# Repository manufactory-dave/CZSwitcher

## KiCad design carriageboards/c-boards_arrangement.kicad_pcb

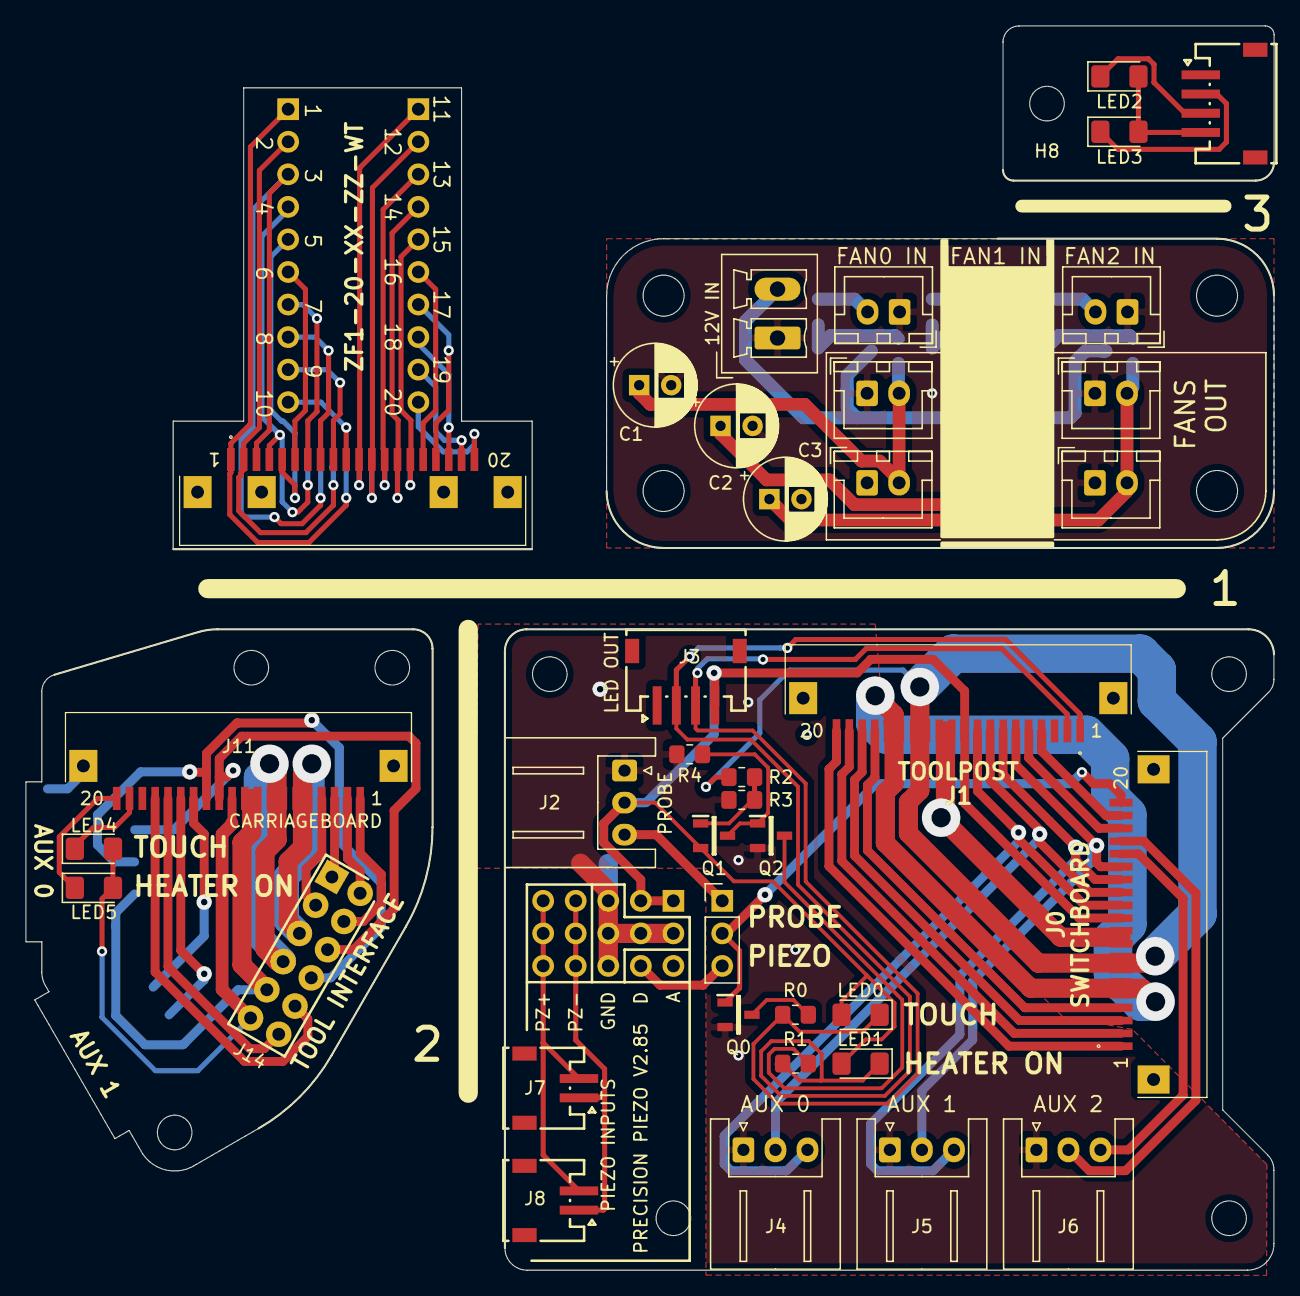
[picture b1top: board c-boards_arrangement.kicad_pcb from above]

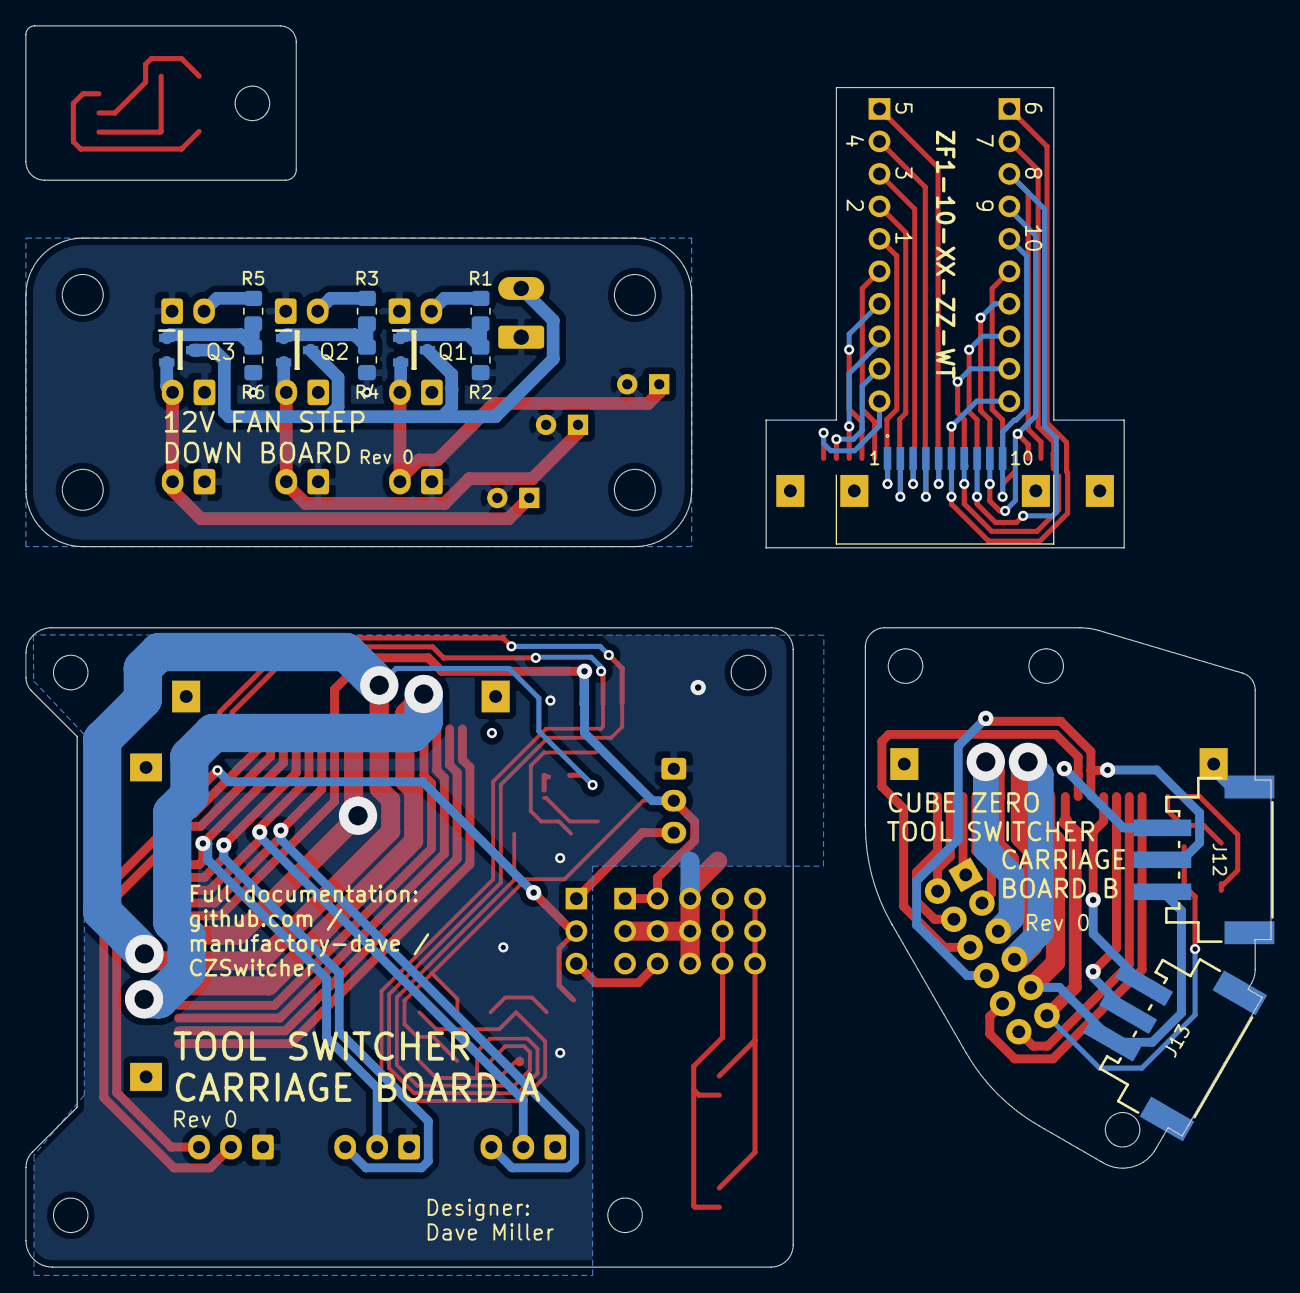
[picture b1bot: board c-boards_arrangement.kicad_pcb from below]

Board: 2 copper layers, 97.4 x 97.1 mm, 68 parts (12 on the bottom side), 75 nets.

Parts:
C1, C2, C3: 100uF_35V_Electro_Radial; CP_Radial_D6.3mm_P2.50mm
H1, H2, H3, H4, H5, H6, H7, H8: MountingHole; MountingHole_2.7mm_M2.5
H1#2, H2#2, H3#2, H4#2: MountingHole; MountingHole_3.2mm_M3
J0: SWITCHBOARD; ZF1-20-XX-ZZ-WT_Handsolder
J1: TOOLPOST; ZF1-20-XX-ZZ-WT_Handsolder
J1#2: 12V IN; PhoenixContact_MCV_1,5_2-G-3.81_1x02_P3.81mm_Vertical
J2: PROBE; JST_XH_S3B-XH-A_1x03_P2.50mm_Horizontal
J2#2: FAN0 IN; JST_XH_B2B-XH-A_1x02_P2.50mm_Vertical
J3, J10: STATUS LED; JST-ZH_S4B-ZR-SM4A-TF
J3#2, J4#2: FAN0 OUT; JST_XH_B2B-XH-A_1x02_P2.50mm_Vertical
J4: AUX 0; JST_XH_S3B-XH-A_1x03_P2.50mm_Horizontal
J5: AUX 1; JST_XH_S3B-XH-A_1x03_P2.50mm_Horizontal
J5#2: FAN1 IN; JST_XH_B2B-XH-A_1x02_P2.50mm_Vertical
J6: AUX 2; JST_XH_S3B-XH-A_1x03_P2.50mm_Horizontal
J6#2, J7#2: FAN1 OUT; JST_XH_B2B-XH-A_1x02_P2.50mm_Vertical
J7: PIEZO 1; JST-ZH_S2B-ZR-SM4A-TF
J8: PIEZO 2; JST-ZH_S2B-ZR-SM4A-TF
J8#2: FAN2 IN; JST_XH_B2B-XH-A_1x02_P2.50mm_Vertical
J9, J10#2: FAN2 OUT; JST_XH_B2B-XH-A_1x02_P2.50mm_Vertical
J11: CARRIAGEBOARD; ZF1-20-XX-ZZ-WT_Handsolder
J12: AUX 0; JST-XH_2.50MM_03x01_SMT
J13: AUX 1; JST-XH_2.50MM_03x01_SMT
J14: TOOL INTERFACE; 813-S1-012-10-014101
JP0: PIEZO / PROBE SELECT; PinHeader_1x03_P2.54mm_Vertical
LED0, LED2, LED4: APTD3216LVBC_D; LED_1206_3216Metric_Pad1.42x1.75mm_HandSolder
LED1, LED3, LED5: APTD3216LSYCK; LED_1206_3216Metric_Pad1.42x1.75mm_HandSolder
PCB0: PrecisionPiezo285; Precision_Piezo_2.85
Q0, Q2: DMN3150L-7; SUPER-SOT-3
Q1: NTR1P02T1G; SUPER-SOT-3
Q1#2, Q2#2, Q3: FDN359BN; SUPER-SOT-3
R0: 39R; R_0805_2012Metric_Pad1.20x1.40mm_HandSolder
R1: 51R; R_0805_2012Metric_Pad1.20x1.40mm_HandSolder
R1#2, R2, R3, R3#2, R5: 39k; R_0805_2012Metric_Pad1.20x1.40mm_HandSolder
R2#2, R4#2, R6: 10k; R_0805_2012Metric_Pad1.20x1.40mm_HandSolder
R4: 220R; R_0805_2012Metric_Pad1.20x1.40mm_HandSolder
ax13, ax17: Conn_01x10; PinHeader_1x10_P2.54mm_Vertical
ax15: ZF1-20-XX-ZZ-WT; ZF1-20-XX-ZZ-WT_Handsolder
ax16: ZF1-10-XX-ZZ-WT; ZF1-10-XX-ZZ-WT_Handsolder

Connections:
+3V3: J0.11, J1.10, J2.2, J3.4, LED0.2, LED1.2, PCB0.1, PCB0.2, Q1.2
+12V: J1#2.2, Q1#2.3, Q2#2.3, Q3.3
+24V: J0.5, J0.6, J1.15, J1.16
/1A: J0.4, J1.17
/1A_1: J11.4, J14.3
/1B: J0.1, J1.20
/1B_1: J11.1, J14.4
/2A: J0.3, J1.18
/2A_1: J11.3, J14.1
/2B: J0.2, J1.19
/2B_1: J11.2, J14.2
/3V3_1: J11.11, J14.11, LED4.2, LED5.2
/24V_1: J11.5, J11.6, J14.5
/AUX0: J0.13, J1.8, J4.2
/AUX0_1: J11.13, J12.2, J14.8
/AUX1: J0.15, J1.6, J5.2
/AUX1_1: J11.15, J13.2
/AUX2: J0.17, J6.2
/FAN0_OUT: C1.1, J3#2.2, J4#2.2, Q1#2.2
/FAN1_OUT: C2.1, J6#2.2, J7#2.2, Q2#2.2
/FAN2_OUT: C3.1, J9.2, J10#2.2, Q3.2
/GND1_1: J11.16, J14.12
/GND_1: J11.9, J11.10, J12.1, J13.1, J14.9
/HEATER_OUT: J0.7, J0.8, J1.13, J1.14, R2.1
/HEATER_OUT_1: J11.7, J11.8, J14.7
/HEATLED-: J1.1, J3.2, LED1.1, R1.1
/HEATLED-_1: J11.20, LED5.1
/PROBE: J0.20, JP0.2, Q0.1
/PROBELED-: J1.2, J3.3, LED0.1, R0.1
/PROBELED-_1: J11.19, LED4.1
/PZ+: J7.2, J8.2, PCB0.5, PCB0.10, PCB0.15
/PZ-: J7.1, J8.1, PCB0.4, PCB0.9, PCB0.14
/THERM_OUT: J0.19, J1.4
/THERM_OUT_1: J11.17, J14.10
/V_AUX0: J0.12, J1.9, J4.3
/V_AUX0_1: J11.12, J12.3, J14.6
/V_AUX1: J0.14, J1.7, J5.3
/V_AUX1_1: J11.14, J13.3
/V_AUX2: J0.16, J6.3
GND: C1.2, C2.2, C3.2, J0.9, J0.10, J1.11, J1.12, J1#2.1, J2.1, J2#2.1, J3#2.1, J4.1, J4#2.1, J5.1, J5#2.1, J6.1, J6#2.1, J7#2.1, J8#2.1, J9.1, J10#2.1, PCB0.3, PCB0.6, PCB0.7, PCB0.8, PCB0.13, Q0.2, Q2.2, R2#2.2, R3.2, R4.2, R4#2.2, R6.2
GND1: J0.18, J1.5
unnamed: J2#2.2, R1#2.1
unnamed: J2.3, JP0.1
unnamed: J5#2.2, R3#2.1
unnamed: J8#2.2, R5.1
unnamed: J10.2, LED3.1
unnamed: J10.3, LED2.1
unnamed: J10.4, LED2.2, LED3.2
unnamed: JP0.3, PCB0.12
unnamed: Q0.3, R0.2
unnamed: Q1.1, Q1#2.1, R1#2.2, R2.2, R2#2.1, R3.1
unnamed: Q1.3, Q2.1, R4.1
unnamed: Q2#2.1, R3#2.2, R4#2.1
unnamed: Q2.3, R1.2
unnamed: Q3.1, R5.2, R6.1
unnamed: ax13.1, ax15.11, ax16.5
unnamed: ax13.2, ax15.12, ax16.4
unnamed: ax13.3, ax15.13, ax16.3
unnamed: ax13.4, ax15.14, ax16.2
unnamed: ax13.5, ax15.15, ax16.1
unnamed: ax13.6, ax15.16
unnamed: ax13.7, ax15.17
unnamed: ax13.8, ax15.18
unnamed: ax13.9, ax15.19
unnamed: ax13.10, ax15.20
unnamed: ax15.1, ax16.6, ax17.1
unnamed: ax15.2, ax16.7, ax17.2
unnamed: ax15.3, ax16.8, ax17.3
unnamed: ax15.4, ax16.9, ax17.4
unnamed: ax15.5, ax16.10, ax17.5
unnamed: ax15.6, ax17.6
unnamed: ax15.7, ax17.7
unnamed: ax15.8, ax17.8
unnamed: ax15.9, ax17.9
unnamed: ax15.10, ax17.10

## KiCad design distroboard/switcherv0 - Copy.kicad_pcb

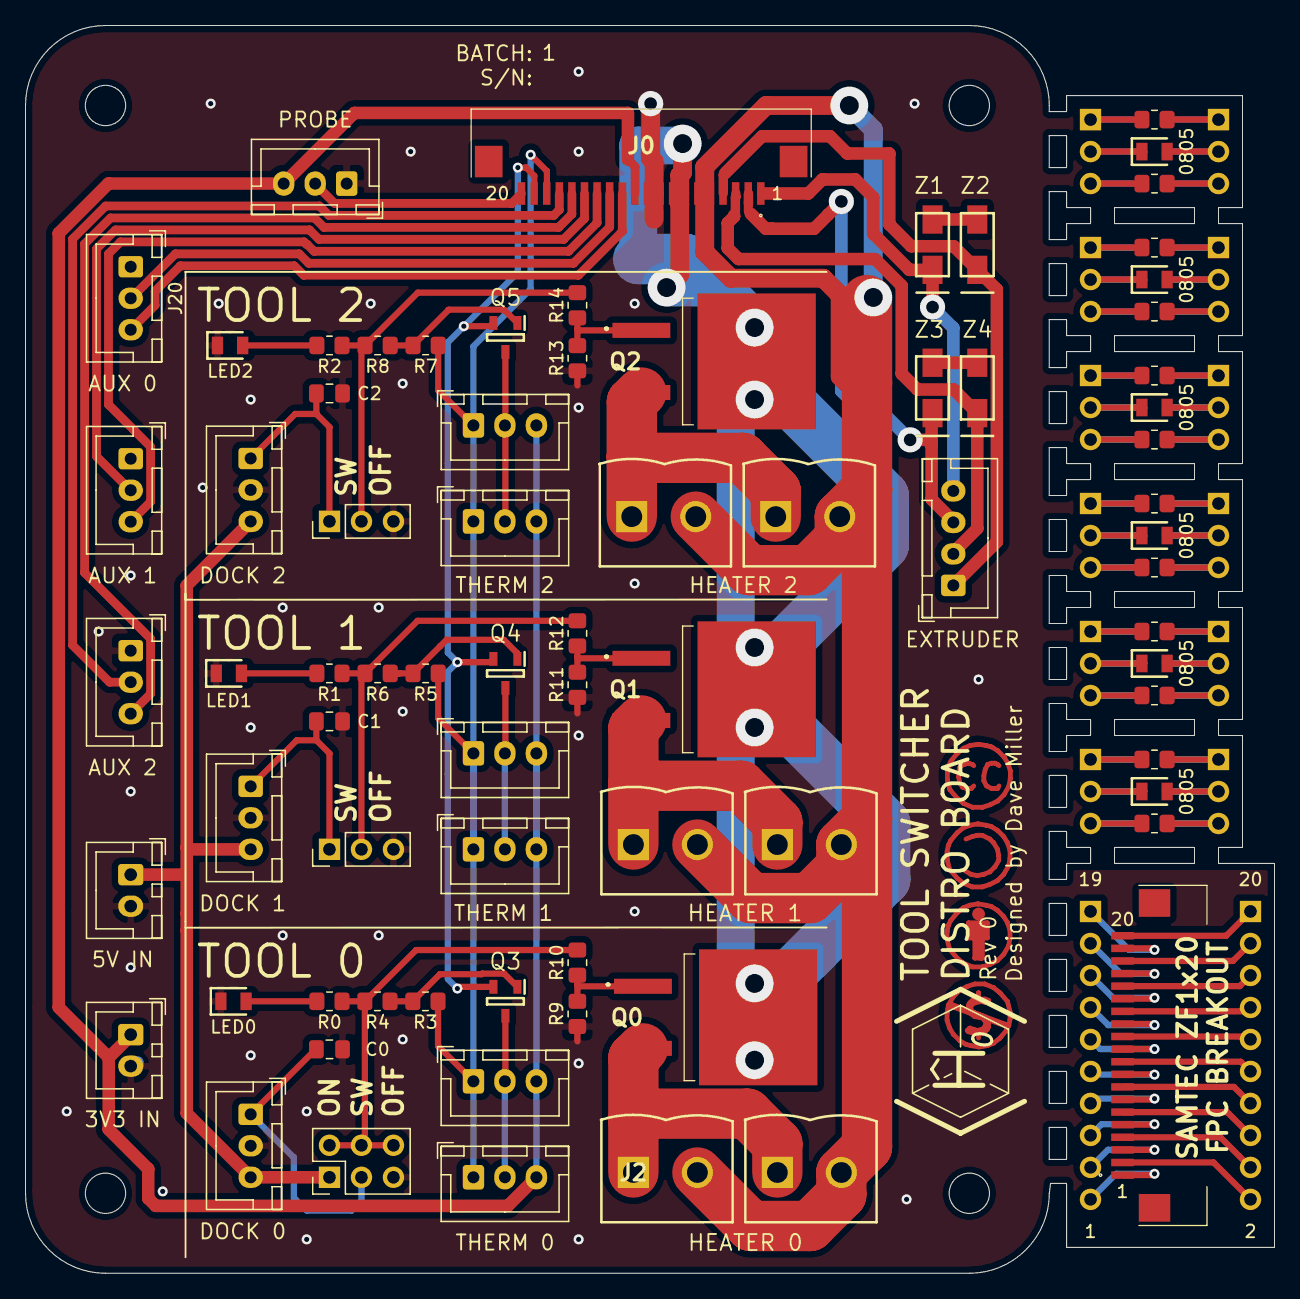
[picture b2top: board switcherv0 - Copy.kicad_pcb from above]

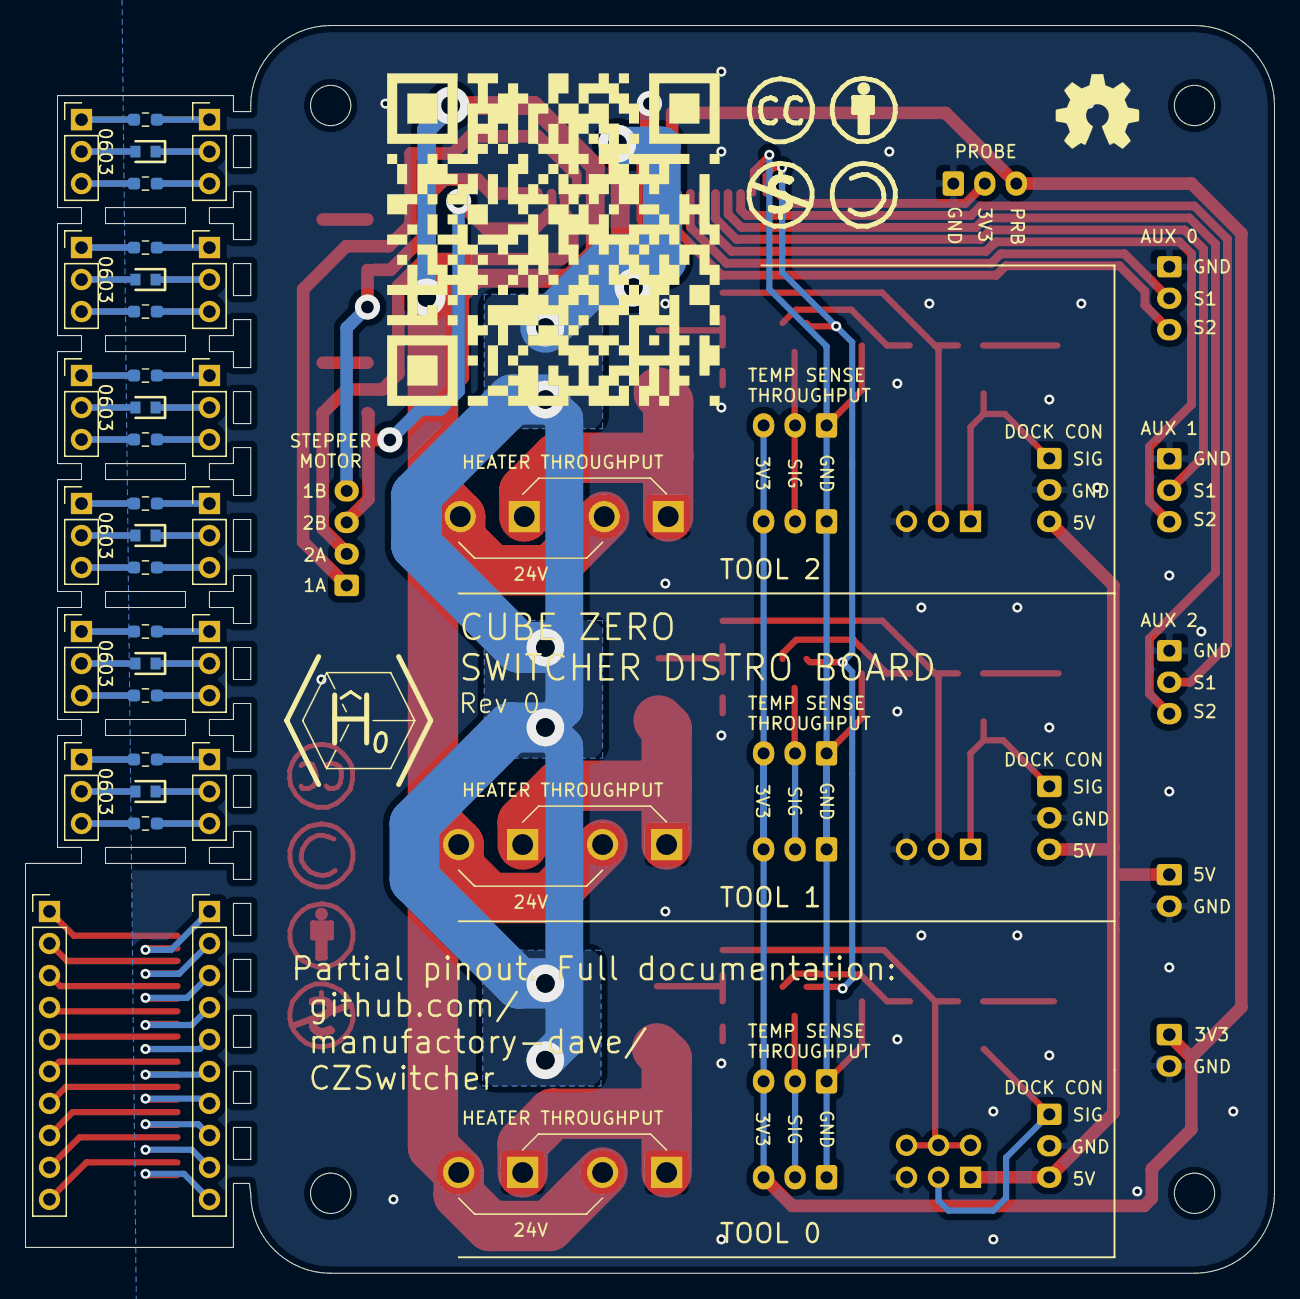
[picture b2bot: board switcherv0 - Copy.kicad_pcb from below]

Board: 2 copper layers, 99.2 x 99.1 mm, 76 parts (8 on the bottom side), 41 nets.

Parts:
C0, C1, C2: 100nF; C_0805_2012Metric_Pad1.18x1.45mm_HandSolder
H0, H1, H2, H3: MountingHole; MountingHole_3.2mm_M3_DIN965
J0: CARRIAGE CONNECTOR; ZF1-20-XX-ZZ-WT
J1: MOTOR IN; JST_XH_B4B-XH-A_1x04_P2.50mm_Vertical
J2, J3: HEATER 0; SHDR2W102P0X508_1X2_1016X835X1230P
J4, J5: HEATER 1; SHDR2W102P0X508_1X2_1016X835X1230P
J6, J7: HEATER 2; SHDR2W102P0X508_1X2_1016X835X1230P
J8, J9: THERM 0; JST_XH_B3B-XH-A_1x03_P2.50mm_Vertical
J10, J11: THERM 1; JST_XH_B3B-XH-A_1x03_P2.50mm_Vertical
J12, J13: THERM 2; JST_XH_B3B-XH-A_1x03_P2.50mm_Vertical
J14: DOCK 0; JST_XH_B3B-XH-A_1x03_P2.50mm_Vertical
J15: DOCK 1; JST_XH_B3B-XH-A_1x03_P2.50mm_Vertical
J16: DOCK 2; JST_XH_B3B-XH-A_1x03_P2.50mm_Vertical
J17: 5V IN; JST_XH_B2B-XH-A_1x02_P2.50mm_Vertical
J18: 3V3 IN; JST_XH_B2B-XH-A_1x02_P2.50mm_Vertical
J19: PROBE; JST_XH_B3B-XH-A_1x03_P2.50mm_Vertical
J20: AUX 0; JST_XH_B3B-XH-A_1x03_P2.50mm_Vertical
J21: AUX 1; JST_XH_B3B-XH-A_1x03_P2.50mm_Vertical
J22: AUX 2; JST_XH_B3B-XH-A_1x03_P2.50mm_Vertical
J**: ZF1-20-XX-ZZ-WT
JP0: TOOL 0 JUMPER; PinHeader_2x03_P2.54mm_Vertical
JP1: TOOL 1 JUMPER; PinHeader_1x03_P2.54mm_Vertical
JP2: TOOL 2 JUMPER; PinHeader_1x03_P2.54mm_Vertical
LED0, LED1, LED2: KP-2012SYC; LEDC2012X110N
LED**: LEDC2012X110N
LED**#2, LED**#4, LED**#5, LED**#7, LED**#9, LED**#11: LEDC1608X120N
LED**#3, LED**#6, LED**#8, LED**#10, LED**#12: LEDC2012X110N
Q0, Q1, Q2: IPB034N03LGATMA1
Q3, Q4, Q5: FDN359BN; SOT95P251X112-3N
QR1: GithubQR; githubQR08
R0, R1, R2: 125; R_0805_2012Metric_Pad1.20x1.40mm_HandSolder
R3, R5, R7: 10k; R_0805_2012Metric_Pad1.20x1.40mm_HandSolder
R4, R6, R8, R10, R12, R14: 22; R_0805_2012Metric_Pad1.20x1.40mm_HandSolder
R9, R11, R13: 10K; R_0805_2012Metric_Pad1.20x1.40mm_HandSolder
U1: CubeZeroLogo; CubeZeroLogoFP
Z1, Z2, Z3, Z4: PTZTE2527A; DIOM5026X220N

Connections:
+3V3: J0.11, J8.3, J9.3, J10.3, J11.3, J12.3, J13.3, J18.1, J19.3
+5V: J14.3, J15.3, J16.3, J17.1, JP0.1
+24V: J0.5, J0.6, J2.2, J3.2, J4.2, J5.2, J6.2, J7.2
/1A: J0.4, J1.1, Z2.1
/1B: J0.1, J1.4, Z1.1
/2A: J0.3, J1.2, Z4.1
/2B: J0.2, J1.3, Z3.1
/AUX0: J0.13, J20.2
/AUX1: J0.15, J21.2
/AUX2: J0.17, J22.2
/HEATER_OUT: J0.7, J0.8, Q0.2, Q1.2, Q2.2
/PROBE: J0.20, J19.2
/THERM_0: J8.2, J9.2, Q3.3
/THERM_1: J10.2, J11.2, Q4.3
/THERM_2: J12.2, J13.2, Q5.3
/THERM_OUT: J0.19, Q3.2, Q4.2, Q5.2
/TOOL0_LOGIC: JP0.2, JP0.4, JP0.6, R0.1, R4.2, R10.2
/TOOL1_LOGIC: JP1.2, R1.1, R6.2, R12.2
/TOOL2_LOGIC: JP2.2, R2.1, R8.2, R14.2
/Tool0Sig: C0.1, J14.1, JP0.3
/Tool1Sig: C1.1, J15.1, JP1.1
/Tool2Sig: C2.1, J16.1, JP2.1
/V_AUX0: J0.12, J20.3
/V_AUX1: J0.14, J21.3
/V_AUX2: J0.16, J22.3
GND: C0.2, C1.2, C2.2, J0.9, J0.10, J14.2, J15.2, J16.2, J17.2, J18.2, J19.1, J20.1, J21.1, J22.1, JP0.5, JP1.3, JP2.3, LED0.1, LED1.1, LED2.1, R9.1, R11.1, R13.1
GND1: J0.18, J8.1, J9.1, J10.1, J11.1, J12.1, J13.1, R3.1, R5.1, R7.1
unnamed: J2.1, J3.1, Q0.3
unnamed: J4.1, J5.1, Q1.3
unnamed: J6.1, J7.1, Q2.3
unnamed: LED0.2, R0.2
unnamed: LED1.2, R1.2
unnamed: LED2.2, R2.2
unnamed: Q0.1, R9.2, R10.1
unnamed: Q1.1, R11.2, R12.1
unnamed: Q2.1, R13.2, R14.1
unnamed: Q3.1, R3.2, R4.1
unnamed: Q4.1, R5.2, R6.1
unnamed: Q5.1, R7.2, R8.1
unnamed: Z1.2, Z2.2
unnamed: Z3.2, Z4.2

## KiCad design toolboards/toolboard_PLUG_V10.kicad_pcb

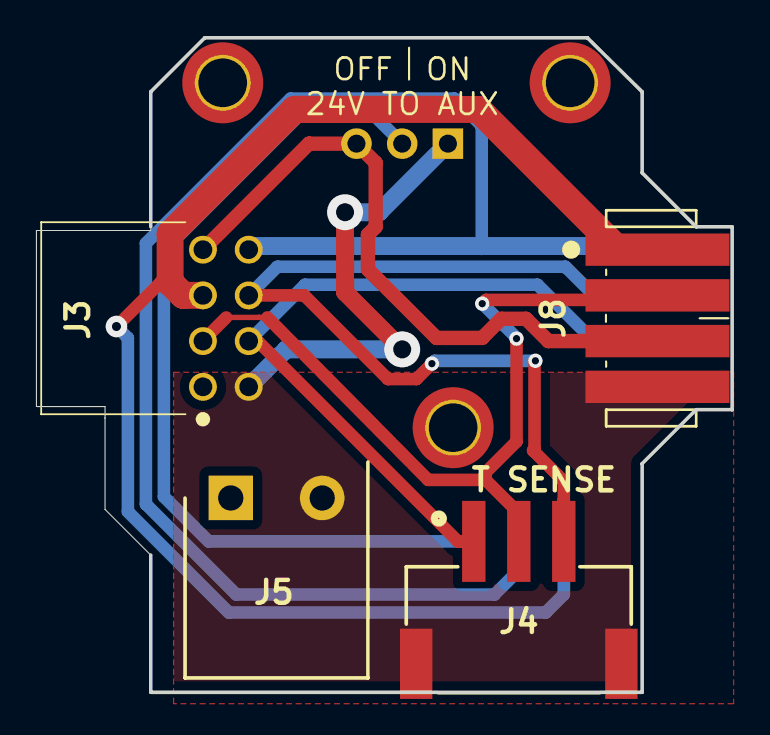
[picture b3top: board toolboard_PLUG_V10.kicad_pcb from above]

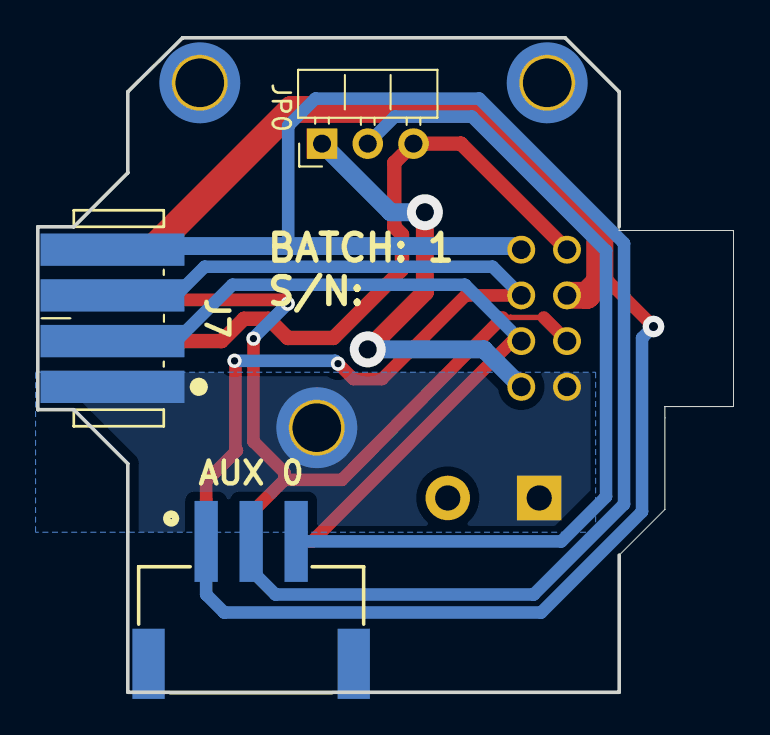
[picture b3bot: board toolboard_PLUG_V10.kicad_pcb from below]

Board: 2 copper layers, 38.6 x 36.4 mm, 10 parts (3 on the bottom side), 9 nets.

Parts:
H3, H4, H5: MountingHole_Pad; MountingHole_2.7mm_M2.5_ISO7380_Pad_TopBottom
J3: INTERBOARD B; SSW-104-XX-YYY-D-RA
J4: T SENSE; JST-XH_2.50MM_03x01_SMT
J5: HEATER; SHDRRA2W102P0X508_1X2_1016X1200X850P
J6: AUX 0; JST-XH_2.50MM_03x01_SMT
J7: DOCK INT 1; 8MM11000402131_handsolder
J8: DOCK INT 2; 8MM11000402131_handsolder
JP0: AUXO 24V SEL; PinHeader_1x03_P2.54mm_Horizontal

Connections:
/3V3_1: J3.6, J4.3, J7.3
/24V_1: J3.2, J4.4, J4.5, J5.2, J8.4, JP0.1
/AUX0_1: J3.8, J6.2, J7.4
/GND1_1: J3.4, J4.1, J7.2
/GND_1: J3.5, J6.1, J8.1
/HEATER_OUT_1: H4.1, J3.1, J5.1, J7.1
/THERM_OUT_1: J3.3, J4.2, J8.2
/V_AUX0_1: J3.7, J8.3, JP0.3
unnamed: J6.3, JP0.2

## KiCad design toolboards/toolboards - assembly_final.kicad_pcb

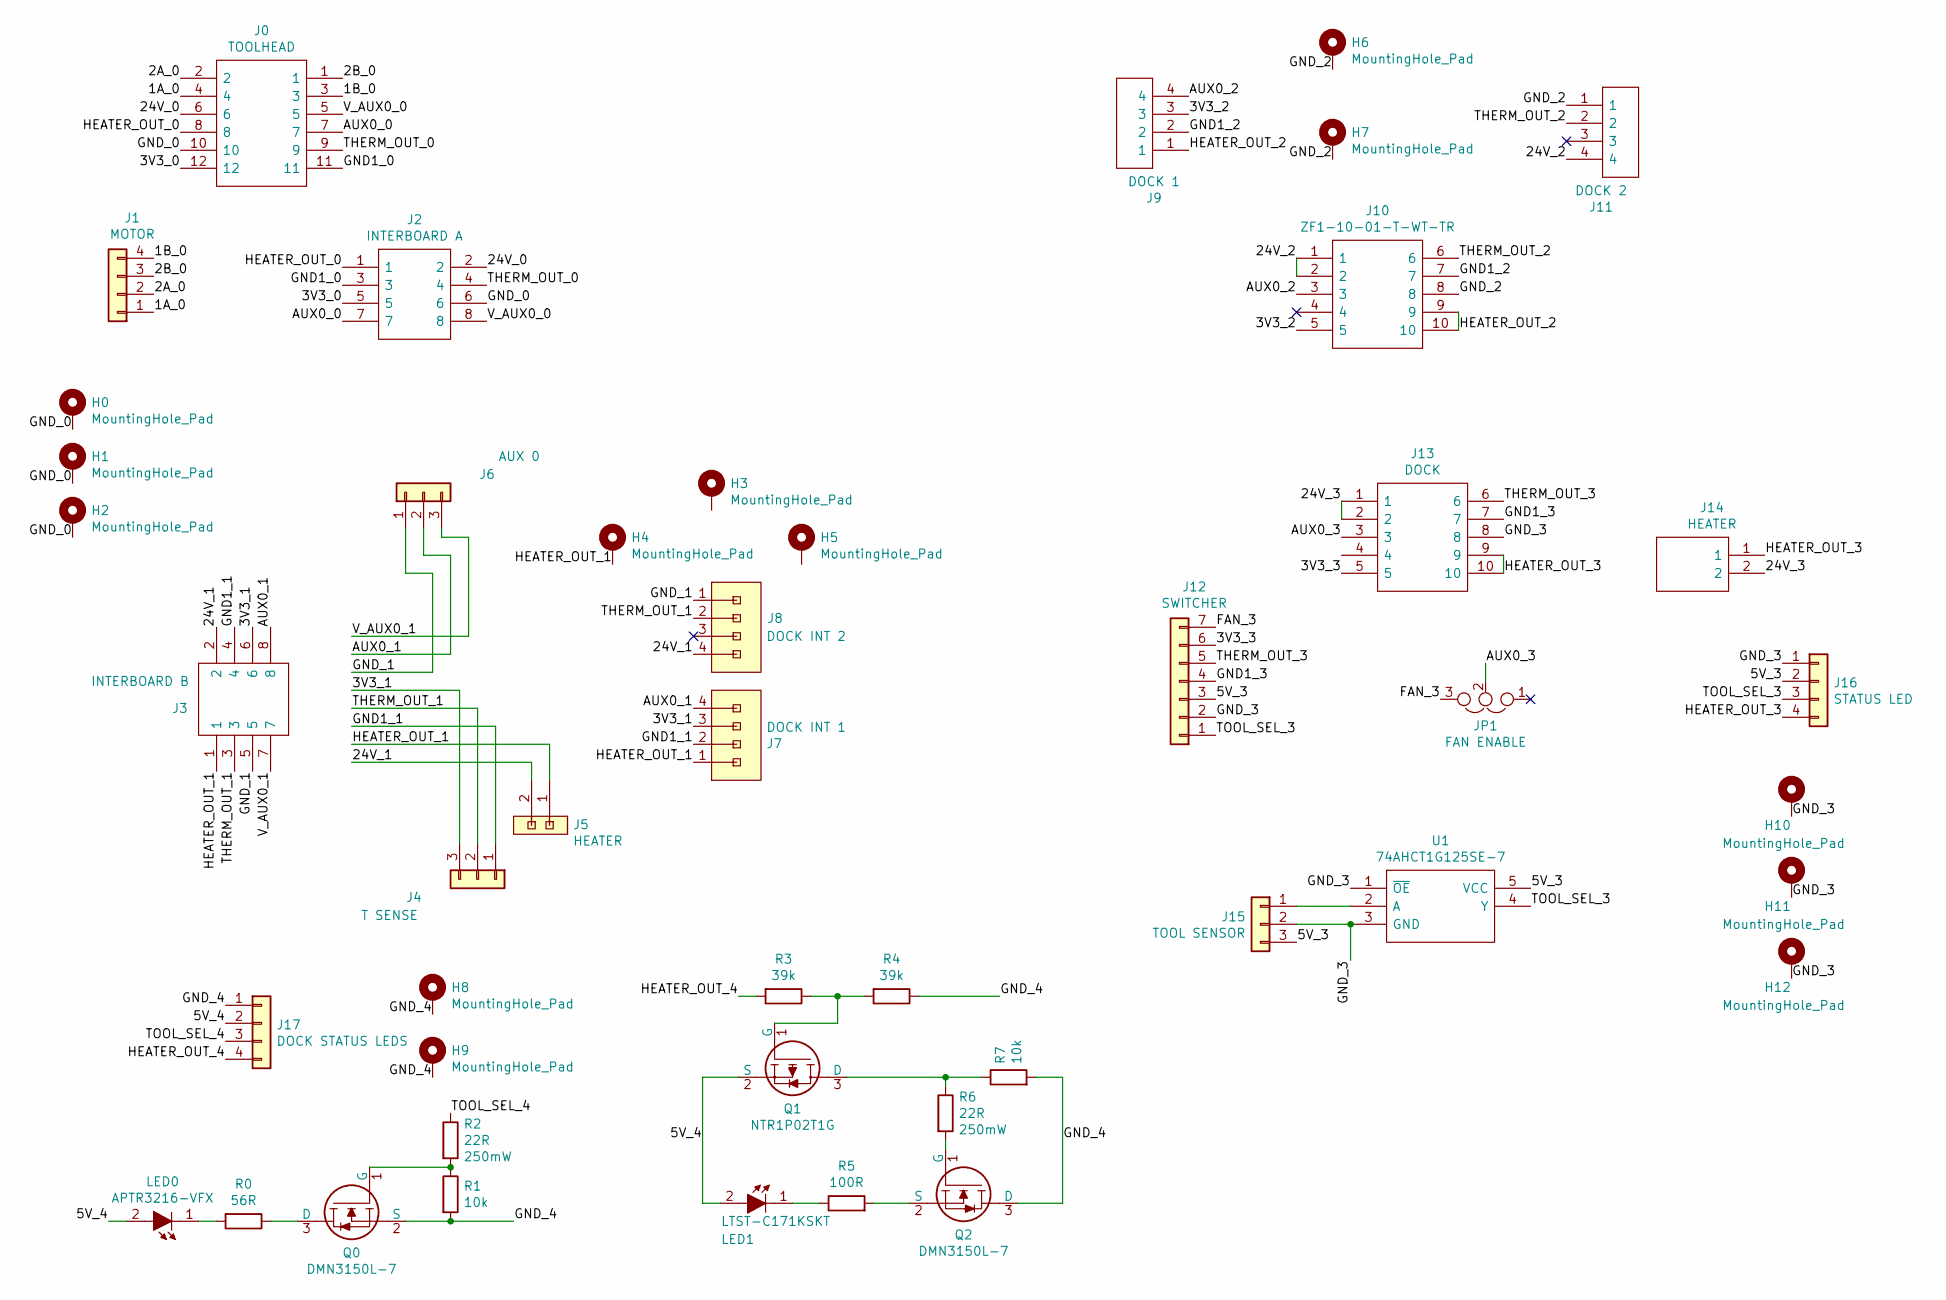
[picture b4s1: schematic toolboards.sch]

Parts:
H0, H1, H2, H3, H4, H5: MountingHole_Pad; MountingHole_2.7mm_M2.5_DIN965_Pad_TopBottom
H6, H7, H8, H9, H10, H11, H12: MountingHole_Pad; MountingHole_3.2mm_M3_DIN965_Pad_TopBottom
J0: TOOLHEAD; 8021001230507101_HS; Manufacturer_Part_Number 802-10-012-30-507101
J1: MOTOR; JST_XH_B4B-XH-A_1x04_P2.50mm_Vertical
J2: INTERBOARD A; HDRV8W64P254_2X4_1016X495X838P; Manufacturer_Part_Number TSW-104-07-T-D
J3: INTERBOARD B; SSW-104-XX-YYY-D-RA; Manufacturer_Part_Number SSW-104-02-T-D-RA
J4: T SENSE; JST-XH_2.50MM_03x01_SMT; Manufacturer_Part_Number S3B-XH-SM4-TB(LF)(SN)
J5, J14: HEATER; SHDRRA2W102P0X508_1X2_1016X1200X850P; Manufacturer_Part_Number 282815-2
J6: AUX 0; JST-XH_2.50MM_03x01_SMT; Manufacturer_Part_Number S3B-XH-SM4-TB(LF)(SN)
J7: DOCK INT 1; 8MM11000402131_handsolder
J8: DOCK INT 2; 8MM11000402131_handsolder
J9: DOCK 1; 811-S1-004-10-017101; Mouser Part Number 437-8MM11000402131
J10: ZF1-10-01-T-WT-TR; ZF1-10-XX-ZZ-WT_Handsolder; Manufacturer_Part_Number ZF1-10-01-T-WT-TR
J11: DOCK 2; 811-S1-004-10-017101; Mouser Part Number 437-8MM11000402131
J12: SWITCHER; JST_XH_B7B-XH-A_1x07_P2.50mm_Vertical
J13: DOCK; ZF1-10-XX-ZZ-WT_Handsolder; Manufacturer_Part_Number ZF1-10-01-T-WT-TR
J15: TOOL SENSOR; JST_XH_B3B-XH-A_1x03_P2.50mm_Vertical
J16: STATUS LED; JST-ZH_S4B-ZR-SM4A-TF; Part Number S4B-ZR-SM4A-TF
J17: DOCK STATUS LEDS; JST-ZH_S4B-ZR-SM4A-TF; Part Number S4B-ZR-SM4A-TF
JP1: FAN ENABLE; PinHeader_1x03_P2.54mm_Vertical
LED0: APTR3216-VFX; LED_1206_3216Metric_Pad1.42x1.75mm_HandSolder; Manufacturer_Part_Number APTR3216-VFX
LED1: LTST-C171KSKT; LED_0805_2012Metric_Pad1.15x1.40mm_HandSolder; Manufacturer_Part_Number LTST-C171KSKT
Q0, Q2: DMN3150L-7; SUPER-SOT-3; Manufacturer_Part_Number DMN3150L-7
Q1: NTR1P02T1G; SUPER-SOT-3; Manufacturer_Part_Number NTR1P02T1G
R0: 56R; R_0805_2012Metric_Pad1.20x1.40mm_HandSolder; Manufacturer_Part_Number RK73B2ATTD560J
R1, R7: 10k; R_0805_2012Metric_Pad1.20x1.40mm_HandSolder; Manufacturer_Part_Number RK73B2ATTE103J
R2, R6: 22R; R_0805_2012Metric_Pad1.20x1.40mm_HandSolder; Manufacturer_Part_Number RK73B2ATTDD220J
R3: 39k; R_0805_2012Metric_Pad1.20x1.40mm_HandSolder; Manufacturer_Part_Number RK73B2ATTE393J
R4: 39k; R_0805_2012Metric_Pad1.20x1.40mm_HandSolder; Manufacturer_Part_Number RK73B2ATTE103J
R5: 100R; R_0805_2012Metric_Pad1.20x1.40mm_HandSolder; Manufacturer_Part_Number RK73B2ATTE101J
U1: 74AHCT1G125SE-7; SOT-23-5_HandSoldering; Manufacturer_Part_Number 74AHCT1G125SE-7

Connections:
/1A_0: J0.4, J1.1
/1B_0: J0.3, J1.4
/2A_0: J0.2, J1.2
/2B_0: J0.1, J1.3
/3V3_0: J0.12, J2.5
/3V3_1: J3.6, J4.3, J7.3
/3V3_2: J9.3, J10.5
/3V3_3: J12.6, J13.5
/5V_3: J12.3, J15.3, J16.2, U1.5 (VCC)
/5V_4: J17.2, LED0.2, LED1.2, Q1.2 (S)
/24V_0: J0.6, J2.2
/24V_1: J3.2, J4.4, J4.5, J5.2, J8.4
/24V_2: J10.1, J10.2, J11.4
/24V_3: J13.1, J13.2, J14.2
/AUX0_0: J0.7, J2.7
/AUX0_1: J3.8, J6.2, J7.4
/AUX0_2: J9.4, J10.3
/AUX0_3: J13.3, JP1.2
/FAN_3: J12.7, JP1.3
/GND1_0: J0.11, J2.3
/GND1_1: J3.4, J4.1, J7.2
/GND1_2: J9.2, J10.7
/GND1_3: J12.4, J13.7
/GND_0: H0.1, H1.1, H2.1, J0.10, J2.6
/GND_1: J3.5, J6.1, J8.1
/GND_2: H6.1, H7.1, J10.8, J10.11, J10.12, J11.1
/GND_3: H10.1, H11.1, H12.1, J12.2, J13.8, J15.2, J16.1, U1.1 (~OE), U1.3 (GND)
/GND_4: H8.1, H9.1, J17.1, Q0.2 (S), Q2.3 (D), R1.2, R4.1, R7.2
/HEATER_OUT_0: J0.8, J2.1
/HEATER_OUT_1: H4.1, J3.1, J5.1, J7.1
/HEATER_OUT_2: J9.1, J10.9, J10.10
/HEATER_OUT_3: J13.9, J13.10, J14.1, J16.4
/HEATER_OUT_4: J17.4, R3.2
/THERM_OUT_0: J0.9, J2.4
/THERM_OUT_1: J3.3, J4.2, J8.2
/THERM_OUT_2: J10.6, J11.2
/THERM_OUT_3: J12.5, J13.6
/TOOL_SEL_3: J12.1, J16.3, U1.4 (Y)
/TOOL_SEL_4: J17.3, R2.1
/V_AUX0_0: J0.5, J2.8
/V_AUX0_1: J3.7, J6.3
unnamed: J15.1, U1.2 (A)
unnamed: LED0.1, R0.2
unnamed: LED1.1, R5.1
unnamed: Q0.1 (G), R1.1, R2.2
unnamed: Q0.3 (D), R0.1
unnamed: Q1.1 (G), R3.1, R4.2
unnamed: Q1.3 (D), R6.1, R7.1
unnamed: Q2.1 (G), R6.2
unnamed: Q2.2 (S), R5.2

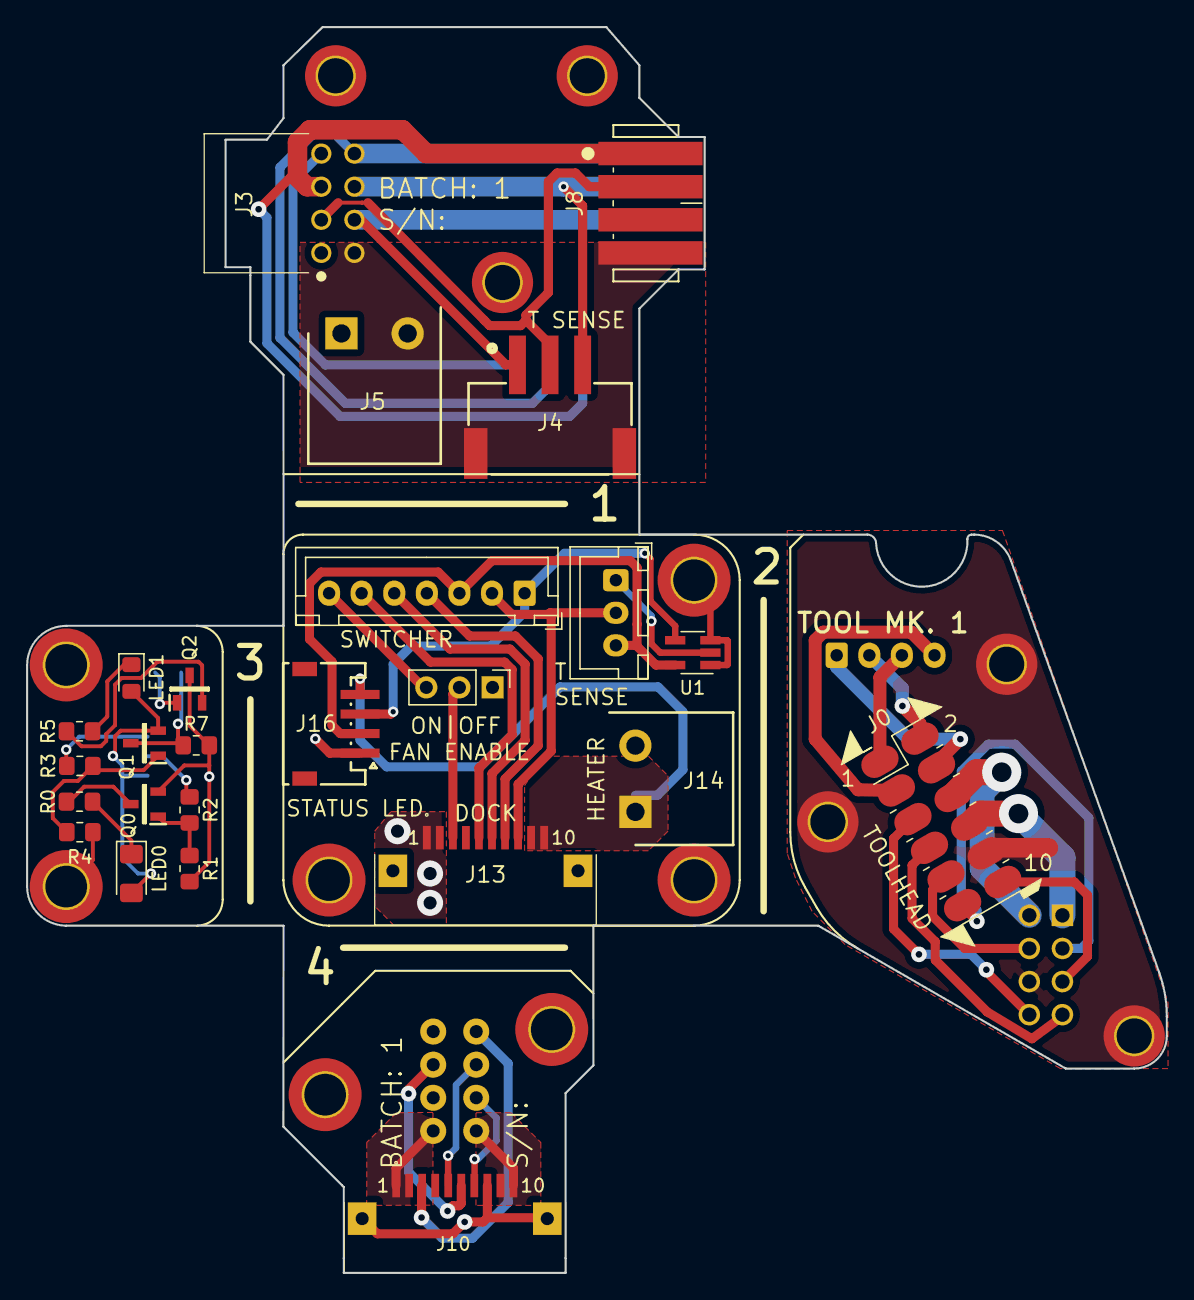
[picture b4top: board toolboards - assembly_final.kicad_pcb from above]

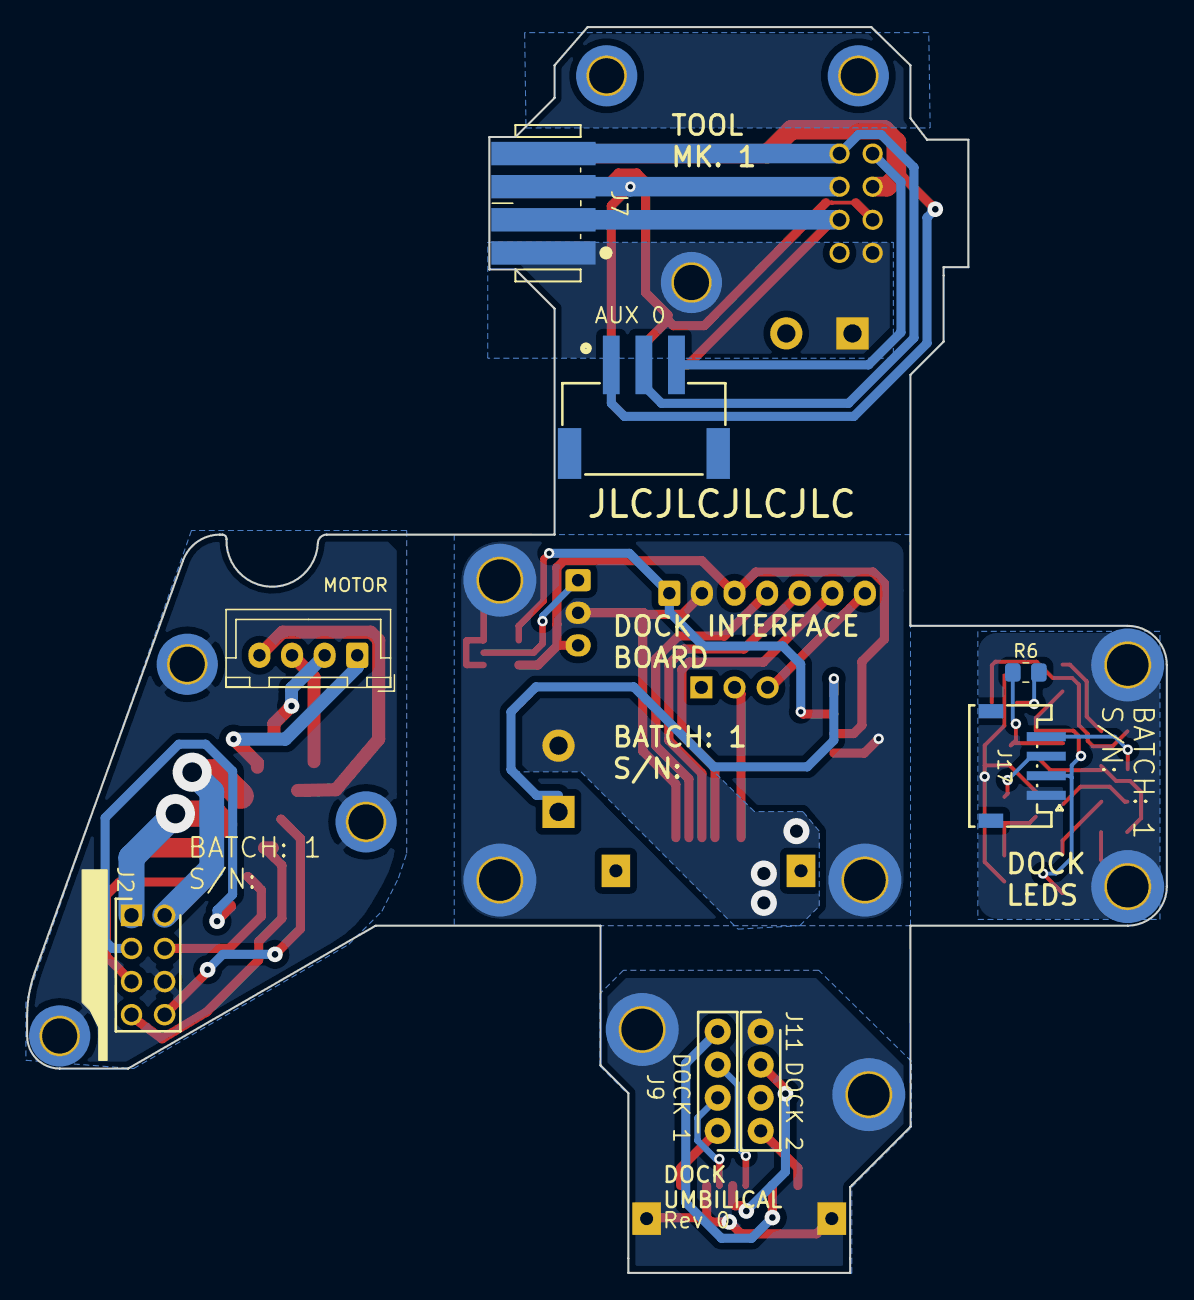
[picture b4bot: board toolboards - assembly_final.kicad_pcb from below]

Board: 2 copper layers, 87.4 x 95.6 mm, 46 parts (8 on the bottom side), 50 nets.

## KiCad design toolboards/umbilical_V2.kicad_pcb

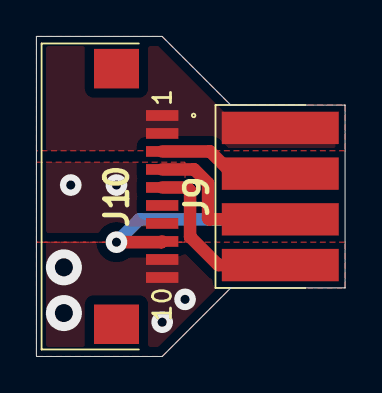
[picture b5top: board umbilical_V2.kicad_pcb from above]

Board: 2 copper layers, 17.1 x 17.8 mm, 3 parts (1 on the bottom side), 7 nets.

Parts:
J9: DOCK 1; 8MM11000402131
J10: ZF1-10-01-T-WT-TR; ZF1-10-XX-ZZ-WT-TR
J11: DOCK 2; 8MM11000402131

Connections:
/3V3_2: J9.3, J10.4
/24V_2: J9.1, J10.1, J10.2
/AUX0_2: J9.4, J10.5
/GND1_2: J9.2, J10.3
/GND_2: J10.7, J11.3
/HEATER_OUT_2: J10.9, J10.10, J11.1
/THERM_OUT_2: J10.8, J11.2
